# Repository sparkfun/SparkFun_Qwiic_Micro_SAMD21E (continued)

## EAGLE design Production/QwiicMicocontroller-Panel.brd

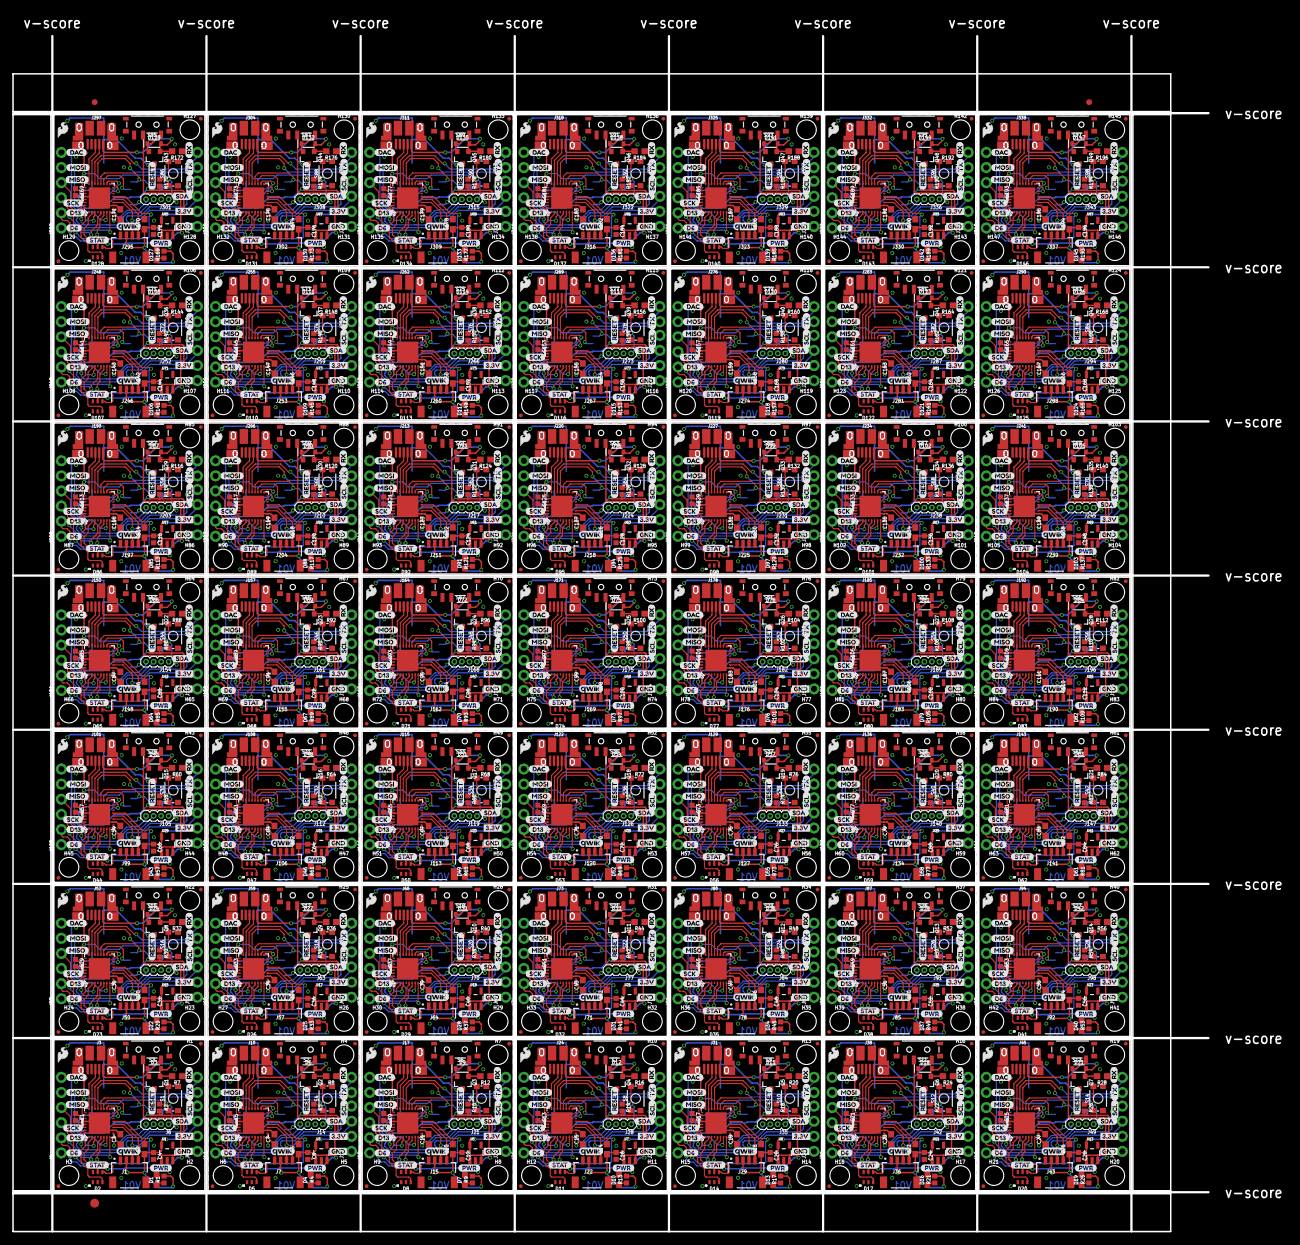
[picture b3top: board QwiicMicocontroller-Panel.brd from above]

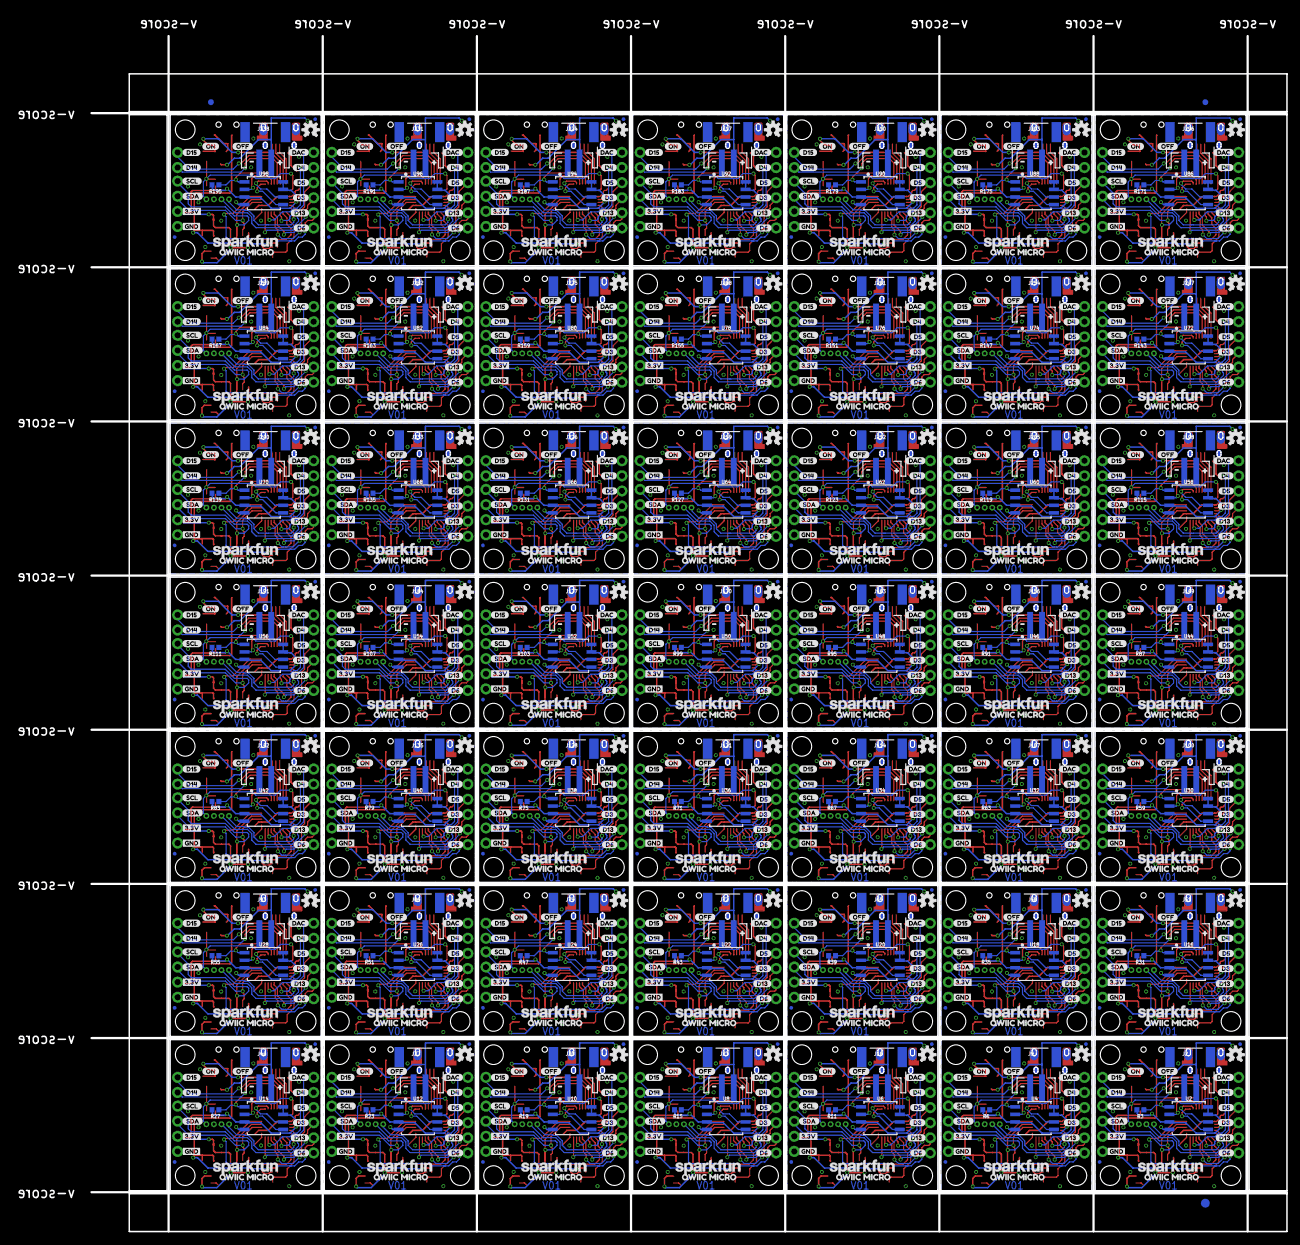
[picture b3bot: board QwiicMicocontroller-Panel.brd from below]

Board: 2 copper layers, 200.9 x 200.9 mm, 3387 parts (1179 on the bottom side), 1470 nets.

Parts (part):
C1, C4, C5, C8, C9, C12, C13, C16, C17, C20, C21, C24, C25, C28, C29, C32, C33, C36, C37, C40, C41, C44, C45, C48, C49, C52, C53, C56, C57, C60, C61, C64, C65, C68, C69, C72, C73, C76, C77, C80, C81, C84, C85, C88, C89, C92, C93, C96, C97, C100, C101, C104, C105, C108, C109, C112, C113, C116, C117, C120, C121, C124, C125, C128, C129, C132, C133, C136, C137, C140, C141, C144, C145, C148, C149, C152, C153, C156, C157, C160, C161, C164, C165, C168, C169, C172, C173, C176, C177, C180, C181, C184, C185, C188, C189, C192, C193, C196: 1.0uF; 0402
C2, C3, C6, C7, C10, C11, C14, C15, C18, C19, C22, C23, C26, C27, C30, C31, C34, C35, C38, C39, C42, C43, C46, C47, C50, C51, C54, C55, C58, C59, C62, C63, C66, C67, C70, C71, C74, C75, C78, C79, C82, C83, C86, C87, C90, C91, C94, C95, C98, C99, C102, C103, C106, C107, C110, C111, C114, C115, C118, C119, C122, C123, C126, C127, C130, C131, C134, C135, C138, C139, C142, C143, C146, C147, C150, C151, C154, C155, C158, C159, C162, C163, C166, C167, C170, C171, C174, C175, C178, C179, C182, C183, C186, C187, C190, C191, C194, C195: 10uF; 0603
D1, D4, D7, D10, D13, D16, D19, D22, D25, D28, D31, D34, D37, D40, D43, D46, D49, D52, D55, D58, D61, D64, D67, D70, D73, D76, D79, D82, D85, D88, D91, D94, D97, D100, D103, D106, D109, D112, D115, D118, D121, D124, D127, D130, D133, D136, D139, D142, D145: RED; LED-0603
D2, D5, D8, D11, D14, D17, D20, D23, D26, D29, D32, D35, D38, D41, D44, D47, D50, D53, D56, D59, D62, D65, D68, D71, D74, D77, D80, D83, D86, D89, D92, D95, D98, D101, D104, D107, D110, D113, D116, D119, D122, D125, D128, D131, D134, D137, D140, D143, D146: APA102-2020
D3, D6, D9, D12, D15, D18, D21, D24, D27, D30, D33, D36, D39, D42, D45, D48, D51, D54, D57, D60, D63, D66, D69, D72, D75, D78, D81, D84, D87, D90, D93, D96, D99, D102, D105, D108, D111, D114, D117, D120, D123, D126, D129, D132, D135, D138, D141, D144, D147: 1A/23V/620mV; SOD-323
E$1, E$2, E$3, E$4: FIDUCIAL-1X2
E$5, E$6: FIDUCIAL-1.5X3
FD1, FD2, FD3, FD4, FD5, FD6, FD7, FD8, FD9, FD10, FD11, FD12, FD13, FD14, FD15, FD16, FD17, FD18, FD19, FD20, FD21, FD22, FD23, FD24, FD25, FD26, FD27, FD28, FD29, FD30, FD31, FD32, FD33, FD34, FD35, FD36, FD37, FD38, FD39, FD40, FD41, FD42, FD43, FD44, FD45, FD46, FD47, FD48, FD49, FD50, FD51, FD52, FD53, FD54, FD55, FD56, FD57, FD58, FD59, FD60, FD61, FD62, FD63, FD64, FD65, FD66, FD67, FD68, FD69, FD70, FD71, FD72, FD73, FD74, FD75, FD76, FD77, FD78, FD79, FD80, FD81, FD82, FD83, FD84, FD85, FD86, FD87, FD88, FD89, FD90, FD91, FD92, FD93, FD94, FD95, FD96, FD97, FD98, FD99, FD100, FD101, FD102, FD103, FD104, FD105, FD106, FD107, FD108, FD109, FD110, FD111, FD112, FD113, FD114, FD115, FD116, FD117, FD118, FD119, FD120, FD121, FD122, FD123, FD124, FD125, FD126, FD127, FD128, FD129, FD130, FD131, FD132, FD133, FD134, FD135, FD136, FD137, FD138, FD139, FD140, FD141, FD142, FD143, FD144, FD145, FD146, FD147, FD148, FD149, FD150, FD151, FD152, FD153, FD154, FD155, FD156, FD157, FD158, FD159, FD160, FD161, FD162, FD163, FD164, FD165, FD166, FD167, FD168, FD169, FD170, FD171, FD172, FD173, FD174, FD175, FD176, FD177, FD178, FD179, FD180, FD181, FD182, FD183, FD184, FD185, FD186, FD187, FD188, FD189, FD190, FD191, FD192, FD193, FD194, FD195, FD196: FIDUCIALUFIDUCIAL; FIDUCIAL-MICRO
H1, H2, H3, H4, H5, H6, H7, H8, H9, H10, H11, H12, H13, H14, H15, H16, H17, H18, H19, H20, H21, H22, H23, H24, H25, H26, H27, H28, H29, H30, H31, H32, H33, H34, H35, H36, H37, H38, H39, H40, H41, H42, H43, H44, H45, H46, H47, H48, H49, H50, H51, H52, H53, H54, H55, H56, H57, H58, H59, H60, H61, H62, H63, H64, H65, H66, H67, H68, H69, H70, H71, H72, H73, H74, H75, H76, H77, H78, H79, H80, H81, H82, H83, H84, H85, H86, H87, H88, H89, H90, H91, H92, H93, H94, H95, H96, H97, H98, H99, H100, H101, H102, H103, H104, H105, H106, H107, H108, H109, H110, H111, H112, H113, H114, H115, H116, H117, H118, H119, H120, H121, H122, H123, H124, H125, H126, H127, H128, H129, H130, H131, H132, H133, H134, H135, H136, H137, H138, H139, H140, H141, H142, H143, H144, H145, H146, H147: STAND-OFF
J1, J7, J15, J22, J29, J36, J43, J50, J57, J64, J71, J78, J85, J92, J99, J106, J113, J120, J127, J134, J141, J148, J155, J162, J169, J176, J183, J190, J197, J204, J211, J218, J225, J232, J239, J246, J253, J260, J267, J274, J281, J288, J295, J302, J309, J316, J323, J330, J337: JST04_1MM_RA
J2, J9, J16, J23, J30, J37, J44, J51, J58, J65, J72, J79, J86, J93, J100, J107, J114, J121, J128, J135, J142, J149, J156, J163, J170, J177, J184, J191, J198, J205, J212, J219, J226, J233, J240, J247, J254, J261, J268, J275, J282, J289, J296, J303, J310, J317, J324, J331, J338: JST-2-SMD
J3, J10, J17, J24, J31, J38, J45, J52, J59, J66, J73, J80, J87, J94, J101, J108, J115, J122, J129, J136, J143, J150, J157, J164, J171, J178, J185, J192, J199, J206, J213, J220, J227, J234, J241, J248, J255, J262, J269, J276, J283, J290, J297, J304, J311, J318, J325, J332, J339: USB-MICROB-PTH-MILL
J4, J11, J18, J25, J32, J39, J46, J53, J60, J67, J74, J81, J88, J95, J102, J109, J116, J123, J130, J137, J144, J151, J158, J165, J172, J179, J186, J193, J200, J207, J214, J221, J228, J235, J242, J249, J256, J263, J270, J277, J284, J291, J298, J305, J312, J319, J326, J333, J340: 1X06_NO_SILK
J5, J12, J19, J26, J33, J40, J47, J54, J61, J68, J75, J82, J89, J96, J103, J110, J117, J124, J131, J138, J145, J152, J159, J166, J173, J180, J187, J194, J201, J208, J215, J222, J229, J236, J243, J250, J257, J264, J271, J278, J285, J292, J299, J306, J313, J320, J327, J334, J341: 1X02_NO_SILK
J6, J14, J21, J28, J35, J42, J49, J56, J63, J70, J77, J84, J91, J98, J105, J112, J119, J126, J133, J140, J147, J154, J161, J168, J175, J182, J189, J196, J203, J210, J217, J224, J231, J238, J245, J252, J259, J266, J273, J280, J287, J294, J301, J308, J315, J322, J329, J336, J343: 1X04_1.27MM
J8, J13, J20, J27, J34, J41, J48, J55, J62, J69, J76, J83, J90, J97, J104, J111, J118, J125, J132, J139, J146, J153, J160, J167, J174, J181, J188, J195, J202, J209, J216, J223, J230, J237, J244, J251, J258, J265, J272, J279, J286, J293, J300, J307, J314, J321, J328, J335, J342: 1X04_NO_SILK
LOGO1, LOGO4, LOGO7, LOGO10, LOGO13, LOGO16, LOGO19, LOGO22, LOGO25, LOGO28, LOGO31, LOGO34, LOGO37, LOGO40, LOGO43, LOGO46, LOGO49, LOGO52, LOGO55, LOGO58, LOGO61, LOGO64, LOGO67, LOGO70, LOGO73, LOGO76, LOGO79, LOGO82, LOGO85, LOGO88, LOGO91, LOGO94, LOGO97, LOGO100, LOGO103, LOGO106, LOGO109, LOGO112, LOGO115, LOGO118, LOGO121, LOGO124, LOGO127, LOGO130, LOGO133, LOGO136, LOGO139, LOGO142, LOGO145: OSHW-LOGOS; OSHW-LOGO-S
LOGO2, LOGO6, LOGO9, LOGO12, LOGO15, LOGO18, LOGO21, LOGO24, LOGO27, LOGO30, LOGO33, LOGO36, LOGO39, LOGO42, LOGO45, LOGO48, LOGO51, LOGO54, LOGO57, LOGO60, LOGO63, LOGO66, LOGO69, LOGO72, LOGO75, LOGO78, LOGO81, LOGO84, LOGO87, LOGO90, LOGO93, LOGO96, LOGO99, LOGO102, LOGO105, LOGO108, LOGO111, LOGO114, LOGO117, LOGO120, LOGO123, LOGO126, LOGO129, LOGO132, LOGO135, LOGO138, LOGO141, LOGO144, LOGO147: SFE_LOGO_NAME.1_INCH; SFE_LOGO_NAME_.1
LOGO3, LOGO5, LOGO8, LOGO11, LOGO14, LOGO17, LOGO20, LOGO23, LOGO26, LOGO29, LOGO32, LOGO35, LOGO38, LOGO41, LOGO44, LOGO47, LOGO50, LOGO53, LOGO56, LOGO59, LOGO62, LOGO65, LOGO68, LOGO71, LOGO74, LOGO77, LOGO80, LOGO83, LOGO86, LOGO89, LOGO92, LOGO95, LOGO98, LOGO101, LOGO104, LOGO107, LOGO110, LOGO113, LOGO116, LOGO119, LOGO122, LOGO125, LOGO128, LOGO131, LOGO134, LOGO137, LOGO140, LOGO143, LOGO146: SFE_LOGO_FLAME.1_INCH; SFE_LOGO_FLAME_.1
Q1, Q2, Q3, Q4, Q5, Q6, Q7, Q8, Q9, Q10, Q11, Q12, Q13, Q14, Q15, Q16, Q17, Q18, Q19, Q20, Q21, Q22, Q23, Q24, Q25, Q26, Q27, Q28, Q29, Q30, Q31, Q32, Q33, Q34, Q35, Q36, Q37, Q38, Q39, Q40, Q41, Q42, Q43, Q44, Q45, Q46, Q47, Q48, Q49: 2.5A/30V/105mΩ; SOT23-3
R1, R4, R9, R13, R17, R21, R25, R29, R33, R37, R41, R45, R49, R53, R57, R61, R65, R69, R73, R77, R81, R85, R89, R93, R97, R101, R105, R109, R113, R117, R121, R125, R129, R133, R137, R141, R145, R149, R153, R157, R161, R165, R169, R173, R177, R181, R185, R189, R193: 1K; 0402
R2, R3, R5, R6, R10, R11, R14, R15, R18, R19, R22, R23, R26, R27, R30, R31, R34, R35, R38, R39, R42, R43, R46, R47, R50, R51, R54, R55, R58, R59, R62, R63, R66, R67, R70, R71, R74, R75, R78, R79, R82, R83, R86, R87, R90, R91, R94, R95, R98, R99, R102, R103, R106, R107, R110, R111, R114, R115, R118, R119, R122, R123, R126, R127, R130, R131, R134, R135, R138, R139, R142, R143, R146, R147, R150, R151, R154, R155, R158, R159, R162, R163, R166, R167, R170, R171, R174, R175, R178, R179, R182, R183, R186, R187, R190, R191, R194, R195: 10k; 0402
R7, R8, R12, R16, R20, R24, R28, R32, R36, R40, R44, R48, R52, R56, R60, R64, R68, R72, R76, R80, R84, R88, R92, R96, R100, R104, R108, R112, R116, R120, R124, R128, R132, R136, R140, R144, R148, R152, R156, R160, R164, R168, R172, R176, R180, R184, R188, R192, R196: 10k; 0603
S1, S4, S6, S8, S10, S12, S14, S16, S18, S20, S22, S24, S26, S28, S30, S32, S34, S36, S38, S40, S42, S44, S46, S48, S50, S52, S54, S56, S58, S60, S62, S64, S66, S68, S70, S72, S74, S76, S78, S80, S82, S84, S86, S88, S90, S92, S94, S96, S98: MOMENTARY-SWITCH-SPST-SMD-4.6X2.8MM; TACTILE_SWITCH_SMD_4.6X2.8MM
S2, S3, S5, S7, S9, S11, S13, S15, S17, S19, S21, S23, S25, S27, S29, S31, S33, S35, S37, S39, S41, S43, S45, S47, S49, S51, S53, S55, S57, S59, S61, S63, S65, S67, S69, S71, S73, S75, S77, S79, S81, S83, S85, S87, S89, S91, S93, S95, S97: SWITCH_SPST_SMD_A
SAMD21E1, SAMD21E2, SAMD21E3, SAMD21E4, SAMD21E5, SAMD21E6, SAMD21E7, SAMD21E8, SAMD21E9, SAMD21E10, SAMD21E11, SAMD21E12, SAMD21E13, SAMD21E14, SAMD21E15, SAMD21E16, SAMD21E17, SAMD21E18, SAMD21E19, SAMD21E20, SAMD21E21, SAMD21E22, SAMD21E23, SAMD21E24, SAMD21E25, SAMD21E26, SAMD21E27, SAMD21E28, SAMD21E29, SAMD21E30, SAMD21E31, SAMD21E32, SAMD21E33, SAMD21E34, SAMD21E35, SAMD21E36, SAMD21E37, SAMD21E38, SAMD21E39, SAMD21E40, SAMD21E41, SAMD21E42, SAMD21E43, SAMD21E44, SAMD21E45, SAMD21E46, SAMD21E47, SAMD21E48, SAMD21E49: SAMD32E; QFN32
TP1, TP2, TP3, TP4, TP5, TP6, TP7, TP8, TP9, TP10, TP11, TP12, TP13, TP14, TP15, TP16, TP17, TP18, TP19, TP20, TP21, TP22, TP23, TP24, TP25, TP26, TP27, TP28, TP29, TP30, TP31, TP32, TP33, TP34, TP35, TP36, TP37, TP38, TP39, TP40, TP41, TP42, TP43, TP44, TP45, TP46, TP47, TP48, TP49, TP50, TP51, TP52, TP53, TP54, TP55, TP56, TP57, TP58, TP59, TP60, TP61, TP62, TP63, TP64, TP65, TP66, TP67, TP68, TP69, TP70, TP71, TP72, TP73, TP74, TP75, TP76, TP77, TP78, TP79, TP80, TP81, TP82, TP83, TP84, TP85, TP86, TP87, TP88, TP89, TP90, TP91, TP92, TP93, TP94, TP95, TP96, TP97, TP98: TEST-POINTTP_15TH_THRU; TP_15TH
U1, U3, U5, U7, U9, U11, U13, U15, U17, U19, U21, U23, U25, U27, U29, U31, U33, U35, U37, U39, U41, U43, U45, U47, U49, U51, U53, U55, U57, U59, U61, U63, U65, U67, U69, U71, U73, U75, U77, U79, U81, U83, U85, U87, U89, U91, U93, U95, U97: 3.3V; SOT23-5
U2, U4, U6, U8, U10, U12, U14, U16, U18, U20, U22, U24, U26, U28, U30, U32, U34, U36, U38, U40, U42, U44, U46, U48, U50, U52, U54, U56, U58, U60, U62, U64, U66, U68, U70, U72, U74, U76, U78, U80, U82, U84, U86, U88, U90, U92, U94, U96, U98: W25Q32FV; SOIC-8
U$1, U$64, U$97, U$130, U$163, U$196, U$229, U$262, U$295, U$328, U$361, U$394, U$427, U$460, U$493, U$526, U$559, U$592, U$625, U$658, U$691, U$724, U$757, U$790, U$823, U$856, U$889, U$922, U$955, U$988, U$1021, U$1054, U$1087, U$1120, U$1153, U$1186, U$1219, U$1252, U$1285, U$1318, U$1351, U$1384, U$1417, U$1450, U$1483, U$1516, U$1549, U$1582, U$1615: QWIIC_LOGO_4MM; QWIIC_4MM
U$2, U$5, U$23, U$50, U$67, U$83, U$100, U$116, U$133, U$149, U$166, U$182, U$199, U$215, U$232, U$248, U$265, U$281, U$298, U$314, U$331, U$347, U$364, U$380, U$397, U$413, U$430, U$446, U$463, U$479, U$496, U$512, U$529, U$545, U$562, U$578, U$595, U$611, U$628, U$644, U$661, U$677, U$694, U$710, U$727, U$743, U$760, U$776, U$793, U$809, U$826, U$842, U$859, U$875, U$892, U$908, U$925, U$941, U$958, U$974, U$991, U$1007, U$1024, U$1040, U$1057, U$1073, U$1090, U$1106, U$1123, U$1139, U$1156, U$1172, U$1189, U$1205, U$1222, U$1238, U$1255, U$1271, U$1288, U$1304, U$1321, U$1337, U$1354, U$1370, U$1387, U$1403, U$1420, U$1436, U$1453, U$1469, U$1486, U$1502, U$1519, U$1535, U$1552, U$1568, U$1585, U$1601: 3#3V1
U$3, U$65, U$98, U$131, U$164, U$197, U$230, U$263, U$296, U$329, U$362, U$395, U$428, U$461, U$494, U$527, U$560, U$593, U$626, U$659, U$692, U$725, U$758, U$791, U$824, U$857, U$890, U$923, U$956, U$989, U$1022, U$1055, U$1088, U$1121, U$1154, U$1187, U$1220, U$1253, U$1286, U$1319, U$1352, U$1385, U$1418, U$1451, U$1484, U$1517, U$1550, U$1583, U$1616: #23
U$4, U$66, U$99, U$132, U$165, U$198, U$231, U$264, U$297, U$330, U$363, U$396, U$429, U$462, U$495, U$528, U$561, U$594, U$627, U$660, U$693, U$726, U$759, U$792, U$825, U$858, U$891, U$924, U$957, U$990, U$1023, U$1056, U$1089, U$1122, U$1155, U$1188, U$1221, U$1254, U$1287, U$1320, U$1353, U$1386, U$1419, U$1452, U$1485, U$1518, U$1551, U$1584, U$1617: #24
U$6, U$10, U$29, U$56, U$68, U$89, U$101, U$122, U$134, U$155, U$167, U$188, U$200, U$221, U$233, U$254, U$266, U$287, U$299, U$320, U$332, U$353, U$365, U$386, U$398, U$419, U$431, U$452, U$464, U$485, U$497, U$518, U$530, U$551, U$563, U$584, U$596, U$617, U$629, U$650, U$662, U$683, U$695, U$716, U$728, U$749, U$761, U$782, U$794, U$815, U$827, U$848, U$860, U$881, U$893, U$914, U$926, U$947, U$959, U$980, U$992, U$1013, U$1025, U$1046, U$1058, U$1079, U$1091, U$1112, U$1124, U$1145, U$1157, U$1178, U$1190, U$1211, U$1223, U$1244, U$1256, U$1277, U$1289, U$1310, U$1322, U$1343, U$1355, U$1376, U$1388, U$1409, U$1421, U$1442, U$1454, U$1475, U$1487, U$1508, U$1520, U$1541, U$1553, U$1574, U$1586, U$1607: D139
U$7, U$36, U$69, U$102, U$135, U$168, U$201, U$234, U$267, U$300, U$333, U$366, U$399, U$432, U$465, U$498, U$531, U$564, U$597, U$630, U$663, U$696, U$729, U$762, U$795, U$828, U$861, U$894, U$927, U$960, U$993, U$1026, U$1059, U$1092, U$1125, U$1158, U$1191, U$1224, U$1257, U$1290, U$1323, U$1356, U$1389, U$1422, U$1455, U$1488, U$1521, U$1554, U$1587: D144
U$8, U$37, U$70, U$103, U$136, U$169, U$202, U$235, U$268, U$301, U$334, U$367, U$400, U$433, U$466, U$499, U$532, U$565, U$598, U$631, U$664, U$697, U$730, U$763, U$796, U$829, U$862, U$895, U$928, U$961, U$994, U$1027, U$1060, U$1093, U$1126, U$1159, U$1192, U$1225, U$1258, U$1291, U$1324, U$1357, U$1390, U$1423, U$1456, U$1489, U$1522, U$1555, U$1588: D155
U$9, U$30, U$38, U$57, U$71, U$90, U$104, U$123, U$137, U$156, U$170, U$189, U$203, U$222, U$236, U$255, U$269, U$288, U$302, U$321, U$335, U$354, U$368, U$387, U$401, U$420, U$434, U$453, U$467, U$486, U$500, U$519, U$533, U$552, U$566, U$585, U$599, U$618, U$632, U$651, U$665, U$684, U$698, U$717, U$731, U$750, U$764, U$783, U$797, U$816, U$830, U$849, U$863, U$882, U$896, U$915, U$929, U$948, U$962, U$981, U$995, U$1014, U$1028, U$1047, U$1061, U$1080, U$1094, U$1113, U$1127, U$1146, U$1160, U$1179, U$1193, U$1212, U$1226, U$1245, U$1259, U$1278, U$1292, U$1311, U$1325, U$1344, U$1358, U$1377, U$1391, U$1410, U$1424, U$1443, U$1457, U$1476, U$1490, U$1509, U$1523, U$1542, U$1556, U$1575, U$1589, U$1608: D610
U$11, U$25, U$39, U$52, U$72, U$85, U$105, U$118, U$138, U$151, U$171, U$184, U$204, U$217, U$237, U$250, U$270, U$283, U$303, U$316, U$336, U$349, U$369, U$382, U$402, U$415, U$435, U$448, U$468, U$481, U$501, U$514, U$534, U$547, U$567, U$580, U$600, U$613, U$633, U$646, U$666, U$679, U$699, U$712, U$732, U$745, U$765, U$778, U$798, U$811, U$831, U$844, U$864, U$877, U$897, U$910, U$930, U$943, U$963, U$976, U$996, U$1009, U$1029, U$1042, U$1062, U$1075, U$1095, U$1108, U$1128, U$1141, U$1161, U$1174, U$1194, U$1207, U$1227, U$1240, U$1260, U$1273, U$1293, U$1306, U$1326, U$1339, U$1359, U$1372, U$1392, U$1405, U$1425, U$1438, U$1458, U$1471, U$1491, U$1504, U$1524, U$1537, U$1557, U$1570, U$1590, U$1603: DAC11
U$12, U$58, U$91, U$124, U$157, U$190, U$223, U$256, U$289, U$322, U$355, U$388, U$421, U$454, U$487, U$520, U$553, U$586, U$619, U$652, U$685, U$718, U$751, U$784, U$817, U$850, U$883, U$916, U$949, U$982, U$1015, U$1048, U$1081, U$1114, U$1147, U$1180, U$1213, U$1246, U$1279, U$1312, U$1345, U$1378, U$1411, U$1444, U$1477, U$1510, U$1543, U$1576, U$1609: RESET22
U$13, U$24, U$40, U$51, U$73, U$84, U$106, U$117, U$139, U$150, U$172, U$183, U$205, U$216, U$238, U$249, U$271, U$282, U$304, U$315, U$337, U$348, U$370, U$381, U$403, U$414, U$436, U$447, U$469, U$480, U$502, U$513, U$535, U$546, U$568, U$579, U$601, U$612, U$634, U$645, U$667, U$678, U$700, U$711, U$733, U$744, U$766, U$777, U$799, U$810, U$832, U$843, U$865, U$876, U$898, U$909, U$931, U$942, U$964, U$975, U$997, U$1008, U$1030, U$1041, U$1063, U$1074, U$1096, U$1107, U$1129, U$1140, U$1162, U$1173, U$1195, U$1206, U$1228, U$1239, U$1261, U$1272, U$1294, U$1305, U$1327, U$1338, U$1360, U$1371, U$1393, U$1404, U$1426, U$1437, U$1459, U$1470, U$1492, U$1503, U$1525, U$1536, U$1558, U$1569, U$1591, U$1602: GND0
U$14, U$41, U$74, U$107, U$140, U$173, U$206, U$239, U$272, U$305, U$338, U$371, U$404, U$437, U$470, U$503, U$536, U$569, U$602, U$635, U$668, U$701, U$734, U$767, U$800, U$833, U$866, U$899, U$932, U$965, U$998, U$1031, U$1064, U$1097, U$1130, U$1163, U$1196, U$1229, U$1262, U$1295, U$1328, U$1361, U$1394, U$1427, U$1460, U$1493, U$1526, U$1559, U$1592: PWR14
U$15, U$42, U$75, U$108, U$141, U$174, U$207, U$240, U$273, U$306, U$339, U$372, U$405, U$438, U$471, U$504, U$537, U$570, U$603, U$636, U$669, U$702, U$735, U$768, U$801, U$834, U$867, U$900, U$933, U$966, U$999, U$1032, U$1065, U$1098, U$1131, U$1164, U$1197, U$1230, U$1263, U$1296, U$1329, U$1362, U$1395, U$1428, U$1461, U$1494, U$1527, U$1560, U$1593: QWIIC_MICRO16
U$16, U$43, U$76, U$109, U$142, U$175, U$208, U$241, U$274, U$307, U$340, U$373, U$406, U$439, U$472, U$505, U$538, U$571, U$604, U$637, U$670, U$703, U$736, U$769, U$802, U$835, U$868, U$901, U$934, U$967, U$1000, U$1033, U$1066, U$1099, U$1132, U$1165, U$1198, U$1231, U$1264, U$1297, U$1330, U$1363, U$1396, U$1429, U$1462, U$1495, U$1528, U$1561, U$1594: RX12
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
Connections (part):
3.3V: C2.1, C4.1, J1.2, J8.2, R1.2, R2.2, R3.2, SAMD21E18.VDDIN, U1.5, U2.3, U2.7, U2.8
3.3V1: C6.1, C8.1, J7.2, J13.2, R4.2, R5.2, R6.2, SAMD21E1.VDDIN, U3.5, U4.3, U4.7, U4.8
3.3V2: C10.1, C12.1, J15.2, J20.2, R9.2, R10.2, R11.2, SAMD21E2.VDDIN, U5.5, U6.3, U6.7, U6.8
3.3V3: C14.1, C16.1, J22.2, J27.2, R13.2, R14.2, R15.2, SAMD21E3.VDDIN, U7.5, U8.3, U8.7, U8.8
3.3V4: C18.1, C20.1, J29.2, J34.2, R17.2, R18.2, R19.2, SAMD21E4.VDDIN, U9.5, U10.3, U10.7, U10.8
3.3V5: C22.1, C24.1, J36.2, J41.2, R21.2, R22.2, R23.2, SAMD21E5.VDDIN, U11.5, U12.3, U12.7, U12.8
3.3V6: C26.1, C28.1, J43.2, J48.2, R25.2, R26.2, R27.2, SAMD21E6.VDDIN, U13.5, U14.3, U14.7, U14.8
3.3V7: C30.1, C32.1, J50.2, J55.2, R29.2, R30.2, R31.2, SAMD21E7.VDDIN, U15.5, U16.3, U16.7, U16.8
3.3V8: C34.1, C36.1, J57.2, J62.2, R33.2, R34.2, R35.2, SAMD21E8.VDDIN, U17.5, U18.3, U18.7, U18.8
3.3V9: C38.1, C40.1, J64.2, J69.2, R37.2, R38.2, R39.2, SAMD21E9.VDDIN, U19.5, U20.3, U20.7, U20.8
3.3V10: C42.1, C44.1, J71.2, J76.2, R41.2, R42.2, R43.2, SAMD21E10.VDDIN, U21.5, U22.3, U22.7, U22.8
3.3V11: C46.1, C48.1, J78.2, J83.2, R45.2, R46.2, R47.2, SAMD21E11.VDDIN, U23.5, U24.3, U24.7, U24.8
3.3V12: C50.1, C52.1, J85.2, J90.2, R49.2, R50.2, R51.2, SAMD21E12.VDDIN, U25.5, U26.3, U26.7, U26.8
3.3V13: C54.1, C56.1, J92.2, J97.2, R53.2, R54.2, R55.2, SAMD21E13.VDDIN, U27.5, U28.3, U28.7, U28.8
3.3V14: C58.1, C60.1, J99.2, J104.2, R57.2, R58.2, R59.2, SAMD21E14.VDDIN, U29.5, U30.3, U30.7, U30.8
3.3V15: C62.1, C64.1, J106.2, J111.2, R61.2, R62.2, R63.2, SAMD21E15.VDDIN, U31.5, U32.3, U32.7, U32.8
3.3V16: C66.1, C68.1, J113.2, J118.2, R65.2, R66.2, R67.2, SAMD21E16.VDDIN, U33.5, U34.3, U34.7, U34.8
3.3V17: C70.1, C72.1, J120.2, J125.2, R69.2, R70.2, R71.2, SAMD21E17.VDDIN, U35.5, U36.3, U36.7, U36.8
3.3V18: C74.1, C76.1, J127.2, J132.2, R73.2, R74.2, R75.2, SAMD21E19.VDDIN, U37.5, U38.3, U38.7, U38.8
3.3V19: C78.1, C80.1, J134.2, J139.2, R77.2, R78.2, R79.2, SAMD21E20.VDDIN, U39.5, U40.3, U40.7, U40.8
3.3V20: C82.1, C84.1, J141.2, J146.2, R81.2, R82.2, R83.2, SAMD21E21.VDDIN, U41.5, U42.3, U42.7, U42.8
3.3V21: C86.1, C88.1, J148.2, J153.2, R85.2, R86.2, R87.2, SAMD21E22.VDDIN, U43.5, U44.3, U44.7, U44.8
3.3V22: C90.1, C92.1, J155.2, J160.2, R89.2, R90.2, R91.2, SAMD21E23.VDDIN, U45.5, U46.3, U46.7, U46.8
3.3V23: C94.1, C96.1, J162.2, J167.2, R93.2, R94.2, R95.2, SAMD21E24.VDDIN, U47.5, U48.3, U48.7, U48.8
3.3V24: C98.1, C100.1, J169.2, J174.2, R97.2, R98.2, R99.2, SAMD21E25.VDDIN, U49.5, U50.3, U50.7, U50.8
3.3V25: C102.1, C104.1, J176.2, J181.2, R101.2, R102.2, R103.2, SAMD21E26.VDDIN, U51.5, U52.3, U52.7, U52.8
3.3V26: C106.1, C108.1, J183.2, J188.2, R105.2, R106.2, R107.2, SAMD21E27.VDDIN, U53.5, U54.3, U54.7, U54.8
3.3V27: C110.1, C112.1, J190.2, J195.2, R109.2, R110.2, R111.2, SAMD21E28.VDDIN, U55.5, U56.3, U56.7, U56.8
3.3V28: C114.1, C116.1, J197.2, J202.2, R113.2, R114.2, R115.2, SAMD21E29.VDDIN, U57.5, U58.3, U58.7, U58.8
3.3V29: C118.1, C120.1, J204.2, J209.2, R117.2, R118.2, R119.2, SAMD21E30.VDDIN, U59.5, U60.3, U60.7, U60.8
3.3V30: C122.1, C124.1, J211.2, J216.2, R121.2, R122.2, R123.2, SAMD21E31.VDDIN, U61.5, U62.3, U62.7, U62.8
3.3V31: C126.1, C128.1, J218.2, J223.2, R125.2, R126.2, R127.2, SAMD21E32.VDDIN, U63.5, U64.3, U64.7, U64.8
3.3V32: C130.1, C132.1, J225.2, J230.2, R129.2, R130.2, R131.2, SAMD21E33.VDDIN, U65.5, U66.3, U66.7, U66.8
3.3V33: C134.1, C136.1, J232.2, J237.2, R133.2, R134.2, R135.2, SAMD21E34.VDDIN, U67.5, U68.3, U68.7, U68.8
3.3V34: C138.1, C140.1, J239.2, J244.2, R137.2, R138.2, R139.2, SAMD21E35.VDDIN, U69.5, U70.3, U70.7, U70.8
3.3V35: C142.1, C144.1, J246.2, J251.2, R141.2, R142.2, R143.2, SAMD21E36.VDDIN, U71.5, U72.3, U72.7, U72.8
3.3V36: C146.1, C148.1, J253.2, J258.2, R145.2, R146.2, R147.2, SAMD21E37.VDDIN, U73.5, U74.3, U74.7, U74.8
3.3V37: C150.1, C152.1, J260.2, J265.2, R149.2, R150.2, R151.2, SAMD21E38.VDDIN, U75.5, U76.3, U76.7, U76.8
3.3V38: C154.1, C156.1, J267.2, J272.2, R153.2, R154.2, R155.2, SAMD21E39.VDDIN, U77.5, U78.3, U78.7, U78.8
3.3V39: C158.1, C160.1, J274.2, J279.2, R157.2, R158.2, R159.2, SAMD21E40.VDDIN, U79.5, U80.3, U80.7, U80.8
3.3V40: C162.1, C164.1, J281.2, J286.2, R161.2, R162.2, R163.2, SAMD21E41.VDDIN, U81.5, U82.3, U82.7, U82.8
3.3V41: C166.1, C168.1, J288.2, J293.2, R165.2, R166.2, R167.2, SAMD21E42.VDDIN, U83.5, U84.3, U84.7, U84.8
3.3V42: C170.1, C172.1, J295.2, J300.2, R169.2, R170.2, R171.2, SAMD21E43.VDDIN, U85.5, U86.3, U86.7, U86.8
3.3V43: C174.1, C176.1, J302.2, J307.2, R173.2, R174.2, R175.2, SAMD21E44.VDDIN, U87.5, U88.3, U88.7, U88.8
3.3V44: C178.1, C180.1, J309.2, J314.2, R177.2, R178.2, R179.2, SAMD21E45.VDDIN, U89.5, U90.3, U90.7, U90.8
3.3V45: C182.1, C184.1, J316.2, J321.2, R181.2, R182.2, R183.2, SAMD21E46.VDDIN, U91.5, U92.3, U92.7, U92.8
3.3V46: C186.1, C188.1, J323.2, J328.2, R185.2, R186.2, R187.2, SAMD21E47.VDDIN, U93.5, U94.3, U94.7, U94.8
3.3V47: C190.1, C192.1, J330.2, J335.2, R189.2, R190.2, R191.2, SAMD21E48.VDDIN, U95.5, U96.3, U96.7, U96.8
3.3V48: C194.1, C196.1, J337.2, J342.2, R193.2, R194.2, R195.2, SAMD21E49.VDDIN, U97.5, U98.3, U98.7, U98.8
!RESET: J6.1, R2.1, S1.3, S1.4, SAMD21E18.NRESET
!RESET1: J14.1, R5.1, S4.3, S4.4, SAMD21E1.NRESET
!RESET2: J21.1, R10.1, S6.3, S6.4, SAMD21E2.NRESET
!RESET3: J28.1, R14.1, S8.3, S8.4, SAMD21E3.NRESET
!RESET4: J35.1, R18.1, S10.3, S10.4, SAMD21E4.NRESET
!RESET5: J42.1, R22.1, S12.3, S12.4, SAMD21E5.NRESET
!RESET6: J49.1, R26.1, S14.3, S14.4, SAMD21E6.NRESET
!RESET7: J56.1, R30.1, S16.3, S16.4, SAMD21E7.NRESET
!RESET8: J63.1, R34.1, S18.3, S18.4, SAMD21E8.NRESET
!RESET9: J70.1, R38.1, S20.3, S20.4, SAMD21E9.NRESET
!RESET10: J77.1, R42.1, S22.3, S22.4, SAMD21E10.NRESET
!RESET11: J84.1, R46.1, S24.3, S24.4, SAMD21E11.NRESET
!RESET12: J91.1, R50.1, S26.3, S26.4, SAMD21E12.NRESET
!RESET13: J98.1, R54.1, S28.3, S28.4, SAMD21E13.NRESET
!RESET14: J105.1, R58.1, S30.3, S30.4, SAMD21E14.NRESET
!RESET15: J112.1, R62.1, S32.3, S32.4, SAMD21E15.NRESET
!RESET16: J119.1, R66.1, S34.3, S34.4, SAMD21E16.NRESET
!RESET17: J126.1, R70.1, S36.3, S36.4, SAMD21E17.NRESET
!RESET18: J133.1, R74.1, S38.3, S38.4, SAMD21E19.NRESET
!RESET19: J140.1, R78.1, S40.3, S40.4, SAMD21E20.NRESET
!RESET20: J147.1, R82.1, S42.3, S42.4, SAMD21E21.NRESET
!RESET21: J154.1, R86.1, S44.3, S44.4, SAMD21E22.NRESET
!RESET22: J161.1, R90.1, S46.3, S46.4, SAMD21E23.NRESET
!RESET23: J168.1, R94.1, S48.3, S48.4, SAMD21E24.NRESET
!RESET24: J175.1, R98.1, S50.3, S50.4, SAMD21E25.NRESET
!RESET25: J182.1, R102.1, S52.3, S52.4, SAMD21E26.NRESET
!RESET26: J189.1, R106.1, S54.3, S54.4, SAMD21E27.NRESET
!RESET27: J196.1, R110.1, S56.3, S56.4, SAMD21E28.NRESET
!RESET28: J203.1, R114.1, S58.3, S58.4, SAMD21E29.NRESET
!RESET29: J210.1, R118.1, S60.3, S60.4, SAMD21E30.NRESET
!RESET30: J217.1, R122.1, S62.3, S62.4, SAMD21E31.NRESET
!RESET31: J224.1, R126.1, S64.3, S64.4, SAMD21E32.NRESET
!RESET32: J231.1, R130.1, S66.3, S66.4, SAMD21E33.NRESET
!RESET33: J238.1, R134.1, S68.3, S68.4, SAMD21E34.NRESET
!RESET34: J245.1, R138.1, S70.3, S70.4, SAMD21E35.NRESET
!RESET35: J252.1, R142.1, S72.3, S72.4, SAMD21E36.NRESET
!RESET36: J259.1, R146.1, S74.3, S74.4, SAMD21E37.NRESET
!RESET37: J266.1, R150.1, S76.3, S76.4, SAMD21E38.NRESET
!RESET38: J273.1, R154.1, S78.3, S78.4, SAMD21E39.NRESET
!RESET39: J280.1, R158.1, S80.3, S80.4, SAMD21E40.NRESET
!RESET40: J287.1, R162.1, S82.3, S82.4, SAMD21E41.NRESET
!RESET41: J294.1, R166.1, S84.3, S84.4, SAMD21E42.NRESET
!RESET42: J301.1, R170.1, S86.3, S86.4, SAMD21E43.NRESET
!RESET43: J308.1, R174.1, S88.3, S88.4, SAMD21E44.NRESET
!RESET44: J315.1, R178.1, S90.3, S90.4, SAMD21E45.NRESET
!RESET45: J322.1, R182.1, S92.3, S92.4, SAMD21E46.NRESET
!RESET46: J329.1, R186.1, S94.3, S94.4, SAMD21E47.NRESET
!RESET47: J336.1, R190.1, S96.3, S96.4, SAMD21E48.NRESET
!RESET48: J343.1, R194.1, S98.3, S98.4, SAMD21E49.NRESET
CI: D2.CKI, SAMD21E18.PA01
CI1: D5.CKI, SAMD21E1.PA01
CI2: D8.CKI, SAMD21E2.PA01
CI3: D11.CKI, SAMD21E3.PA01
CI4: D14.CKI, SAMD21E4.PA01
CI5: D17.CKI, SAMD21E5.PA01
CI6: D20.CKI, SAMD21E6.PA01
CI7: D23.CKI, SAMD21E7.PA01
CI8: D26.CKI, SAMD21E8.PA01
CI9: D29.CKI, SAMD21E9.PA01
CI10: D32.CKI, SAMD21E10.PA01
CI11: D35.CKI, SAMD21E11.PA01
CI12: D38.CKI, SAMD21E12.PA01
CI13: D41.CKI, SAMD21E13.PA01
CI14: D44.CKI, SAMD21E14.PA01
CI15: D47.CKI, SAMD21E15.PA01
CI16: D50.CKI, SAMD21E16.PA01
CI17: D53.CKI, SAMD21E17.PA01
CI18: D56.CKI, SAMD21E19.PA01
CI19: D59.CKI, SAMD21E20.PA01
CI20: D62.CKI, SAMD21E21.PA01
CI21: D65.CKI, SAMD21E22.PA01
CI22: D68.CKI, SAMD21E23.PA01
CI23: D71.CKI, SAMD21E24.PA01
CI24: D74.CKI, SAMD21E25.PA01
CI25: D77.CKI, SAMD21E26.PA01
CI26: D80.CKI, SAMD21E27.PA01
CI27: D83.CKI, SAMD21E28.PA01
CI28: D86.CKI, SAMD21E29.PA01
CI29: D89.CKI, SAMD21E30.PA01
CI30: D92.CKI, SAMD21E31.PA01
CI31: D95.CKI, SAMD21E32.PA01
CI32: D98.CKI, SAMD21E33.PA01
CI33: D101.CKI, SAMD21E34.PA01
CI34: D104.CKI, SAMD21E35.PA01
CI35: D107.CKI, SAMD21E36.PA01
CI36: D110.CKI, SAMD21E37.PA01
CI37: D113.CKI, SAMD21E38.PA01
CI38: D116.CKI, SAMD21E39.PA01
CI39: D119.CKI, SAMD21E40.PA01
CI40: D122.CKI, SAMD21E41.PA01
CI41: D125.CKI, SAMD21E42.PA01
CI42: D128.CKI, SAMD21E43.PA01
CI43: D131.CKI, SAMD21E44.PA01
CI44: D134.CKI, SAMD21E45.PA01
CI45: D137.CKI, SAMD21E46.PA01
CI46: D140.CKI, SAMD21E47.PA01
CI47: D143.CKI, SAMD21E48.PA01
CI48: D146.CKI, SAMD21E49.PA01
D1: J11.1, SAMD21E1.PA04
D2: J11.2, SAMD21E1.PA10
D3: J18.1, SAMD21E2.PA04
D4: J18.2, SAMD21E2.PA10
D5: J25.1, SAMD21E3.PA04
D6: J4.1, SAMD21E18.PA04
D7: J25.2, SAMD21E3.PA10
D8: J32.1, SAMD21E4.PA04
D9: J32.2, SAMD21E4.PA10
D10: J39.1, SAMD21E5.PA04
D11: J39.2, SAMD21E5.PA10
D12: J46.1, SAMD21E6.PA04
D13: J4.2, SAMD21E18.PA10
D14: J46.2, SAMD21E6.PA10
D15: J53.1, SAMD21E7.PA04
D16: J53.2, SAMD21E7.PA10
D17: J60.1, SAMD21E8.PA04
D18: J60.2, SAMD21E8.PA10
D19: J67.1, SAMD21E9.PA04
D20: J67.2, SAMD21E9.PA10
D21: J74.1, SAMD21E10.PA04
D22: J74.2, SAMD21E10.PA10
D23: J81.1, SAMD21E11.PA04
D24: J81.2, SAMD21E11.PA10
D25: J88.1, SAMD21E12.PA04
D26: J88.2, SAMD21E12.PA10
D27: J95.1, SAMD21E13.PA04
D28: J95.2, SAMD21E13.PA10
D29: J102.1, SAMD21E14.PA04
D30: J102.2, SAMD21E14.PA10
D31: J109.1, SAMD21E15.PA04
D32: J109.2, SAMD21E15.PA10
D33: J116.1, SAMD21E16.PA04
D34: J116.2, SAMD21E16.PA10
D35: J123.1, SAMD21E17.PA04
D36: J123.2, SAMD21E17.PA10
D37: J130.1, SAMD21E19.PA04
D38: J130.2, SAMD21E19.PA10
D39: J137.1, SAMD21E20.PA04
D40: J137.2, SAMD21E20.PA10
D41: J144.1, SAMD21E21.PA04
D42: J144.2, SAMD21E21.PA10
D43: J151.1, SAMD21E22.PA04
D44: J151.2, SAMD21E22.PA10
D45: J158.1, SAMD21E23.PA04
D46: J158.2, SAMD21E23.PA10
D47: J165.1, SAMD21E24.PA04
D48: J165.2, SAMD21E24.PA10
D49: J172.1, SAMD21E25.PA04
D50: J172.2, SAMD21E25.PA10
D51: J179.1, SAMD21E26.PA04
D52: J179.2, SAMD21E26.PA10
D53: J186.1, SAMD21E27.PA04
D54: J186.2, SAMD21E27.PA10
D55: J193.1, SAMD21E28.PA04
D56: J193.2, SAMD21E28.PA10
D57: J200.1, SAMD21E29.PA04
D58: J200.2, SAMD21E29.PA10
D59: J207.1, SAMD21E30.PA04
D60: J207.2, SAMD21E30.PA10
D61: J214.1, SAMD21E31.PA04
D62: J214.2, SAMD21E31.PA10
D63: J221.1, SAMD21E32.PA04
D64: J221.2, SAMD21E32.PA10
D65: J228.1, SAMD21E33.PA04
D66: J228.2, SAMD21E33.PA10
D67: J235.1, SAMD21E34.PA04
D68: J235.2, SAMD21E34.PA10
D69: J242.1, SAMD21E35.PA04
D70: J242.2, SAMD21E35.PA10
D71: J249.1, SAMD21E36.PA04
D72: J249.2, SAMD21E36.PA10
D73: J256.1, SAMD21E37.PA04
D74: J256.2, SAMD21E37.PA10
D75: J263.1, SAMD21E38.PA04
D76: J263.2, SAMD21E38.PA10
D77: J270.1, SAMD21E39.PA04
D78: J270.2, SAMD21E39.PA10
D79: J277.1, SAMD21E40.PA04
D80: J277.2, SAMD21E40.PA10
D81: J284.1, SAMD21E41.PA04
D82: J284.2, SAMD21E41.PA10
D83: J291.1, SAMD21E42.PA04
D84: J291.2, SAMD21E42.PA10
D85: J298.1, SAMD21E43.PA04
D86: J298.2, SAMD21E43.PA10
D87: J305.1, SAMD21E44.PA04
D88: J305.2, SAMD21E44.PA10
D89: J312.1, SAMD21E45.PA04
D90: J312.2, SAMD21E45.PA10
D91: J319.1, SAMD21E46.PA04
D92: J319.2, SAMD21E46.PA10
D93: J326.1, SAMD21E47.PA04
D94: J326.2, SAMD21E47.PA10
D95: J333.1, SAMD21E48.PA04
D96: J333.2, SAMD21E48.PA10
D97: J340.1, SAMD21E49.PA04
D98: J340.2, SAMD21E49.PA10
D+: J3.D+, SAMD21E18.PA25
D+1: J10.D+, SAMD21E1.PA25
D+2: J17.D+, SAMD21E2.PA25
D+3: J24.D+, SAMD21E3.PA25
D+4: J31.D+, SAMD21E4.PA25
D+5: J38.D+, SAMD21E5.PA25
D+6: J45.D+, SAMD21E6.PA25
D+7: J52.D+, SAMD21E7.PA25
D+8: J59.D+, SAMD21E8.PA25
D+9: J66.D+, SAMD21E9.PA25
D+10: J73.D+, SAMD21E10.PA25
D+11: J80.D+, SAMD21E11.PA25
D+12: J87.D+, SAMD21E12.PA25
D+13: J94.D+, SAMD21E13.PA25
D+14: J101.D+, SAMD21E14.PA25
D+15: J108.D+, SAMD21E15.PA25
D+16: J115.D+, SAMD21E16.PA25
D+17: J122.D+, SAMD21E17.PA25
D+18: J129.D+, SAMD21E19.PA25
D+19: J136.D+, SAMD21E20.PA25
D+20: J143.D+, SAMD21E21.PA25
D+21: J150.D+, SAMD21E22.PA25
D+22: J157.D+, SAMD21E23.PA25
D+23: J164.D+, SAMD21E24.PA25
D+24: J171.D+, SAMD21E25.PA25
D+25: J178.D+, SAMD21E26.PA25
D+26: J185.D+, SAMD21E27.PA25
D+27: J192.D+, SAMD21E28.PA25
D+28: J199.D+, SAMD21E29.PA25
D+29: J206.D+, SAMD21E30.PA25
D+30: J213.D+, SAMD21E31.PA25
D+31: J220.D+, SAMD21E32.PA25
D+32: J227.D+, SAMD21E33.PA25
D+33: J234.D+, SAMD21E34.PA25
D+34: J241.D+, SAMD21E35.PA25
D+35: J248.D+, SAMD21E36.PA25
D+36: J255.D+, SAMD21E37.PA25
D+37: J262.D+, SAMD21E38.PA25
D+38: J269.D+, SAMD21E39.PA25
D+39: J276.D+, SAMD21E40.PA25
D+40: J283.D+, SAMD21E41.PA25
D+41: J290.D+, SAMD21E42.PA25
D+42: J297.D+, SAMD21E43.PA25
D+43: J304.D+, SAMD21E44.PA25
D+44: J311.D+, SAMD21E45.PA25
D+45: J318.D+, SAMD21E46.PA25
D+46: J325.D+, SAMD21E47.PA25
D+47: J332.D+, SAMD21E48.PA25
D+48: J339.D+, SAMD21E49.PA25
D-: J3.D-, SAMD21E18.PA24
D-1: J10.D-, SAMD21E1.PA24
D-2: J17.D-, SAMD21E2.PA24
D-3: J24.D-, SAMD21E3.PA24
D-4: J31.D-, SAMD21E4.PA24
D-5: J38.D-, SAMD21E5.PA24
D-6: J45.D-, SAMD21E6.PA24
D-7: J52.D-, SAMD21E7.PA24
D-8: J59.D-, SAMD21E8.PA24
D-9: J66.D-, SAMD21E9.PA24
D-10: J73.D-, SAMD21E10.PA24
D-11: J80.D-, SAMD21E11.PA24
D-12: J87.D-, SAMD21E12.PA24
D-13: J94.D-, SAMD21E13.PA24
D-14: J101.D-, SAMD21E14.PA24
D-15: J108.D-, SAMD21E15.PA24
D-16: J115.D-, SAMD21E16.PA24
D-17: J122.D-, SAMD21E17.PA24
D-18: J129.D-, SAMD21E19.PA24
D-19: J136.D-, SAMD21E20.PA24
D-20: J143.D-, SAMD21E21.PA24
D-21: J150.D-, SAMD21E22.PA24
D-22: J157.D-, SAMD21E23.PA24
D-23: J164.D-, SAMD21E24.PA24
D-24: J171.D-, SAMD21E25.PA24
D-25: J178.D-, SAMD21E26.PA24
D-26: J185.D-, SAMD21E27.PA24
D-27: J192.D-, SAMD21E28.PA24
D-28: J199.D-, SAMD21E29.PA24
D-29: J206.D-, SAMD21E30.PA24
D-30: J213.D-, SAMD21E31.PA24
D-31: J220.D-, SAMD21E32.PA24
D-32: J227.D-, SAMD21E33.PA24
D-33: J234.D-, SAMD21E34.PA24
D-34: J241.D-, SAMD21E35.PA24
D-35: J248.D-, SAMD21E36.PA24
D-36: J255.D-, SAMD21E37.PA24
D-37: J262.D-, SAMD21E38.PA24
D-38: J269.D-, SAMD21E39.PA24
D-39: J276.D-, SAMD21E40.PA24
D-40: J283.D-, SAMD21E41.PA24
D-41: J290.D-, SAMD21E42.PA24
D-42: J297.D-, SAMD21E43.PA24
D-43: J304.D-, SAMD21E44.PA24
D-44: J311.D-, SAMD21E45.PA24
D-45: J318.D-, SAMD21E46.PA24
D-46: J325.D-, SAMD21E47.PA24
D-47: J332.D-, SAMD21E48.PA24
D-48: J339.D-, SAMD21E49.PA24
DAC: J4.6, SAMD21E18.PA02
DAC1: J11.6, SAMD21E1.PA02
DAC2: J18.6, SAMD21E2.PA02
DAC3: J25.6, SAMD21E3.PA02
DAC4: J32.6, SAMD21E4.PA02
DAC5: J39.6, SAMD21E5.PA02
DAC6: J46.6, SAMD21E6.PA02
DAC7: J53.6, SAMD21E7.PA02
DAC8: J60.6, SAMD21E8.PA02
DAC9: J67.6, SAMD21E9.PA02
DAC10: J74.6, SAMD21E10.PA02
DAC11: J81.6, SAMD21E11.PA02
DAC12: J88.6, SAMD21E12.PA02
DAC13: J95.6, SAMD21E13.PA02
DAC14: J102.6, SAMD21E14.PA02
DAC15: J109.6, SAMD21E15.PA02
DAC16: J116.6, SAMD21E16.PA02
DAC17: J123.6, SAMD21E17.PA02
DAC18: J130.6, SAMD21E19.PA02
DAC19: J137.6, SAMD21E20.PA02
DAC20: J144.6, SAMD21E21.PA02
DAC21: J151.6, SAMD21E22.PA02
DAC22: J158.6, SAMD21E23.PA02
DAC23: J165.6, SAMD21E24.PA02
DAC24: J172.6, SAMD21E25.PA02
DAC25: J179.6, SAMD21E26.PA02
DAC26: J186.6, SAMD21E27.PA02
DAC27: J193.6, SAMD21E28.PA02
DAC28: J200.6, SAMD21E29.PA02
DAC29: J207.6, SAMD21E30.PA02
DAC30: J214.6, SAMD21E31.PA02
DAC31: J221.6, SAMD21E32.PA02
DAC32: J228.6, SAMD21E33.PA02
DAC33: J235.6, SAMD21E34.PA02
DAC34: J242.6, SAMD21E35.PA02
DAC35: J249.6, SAMD21E36.PA02
DAC36: J256.6, SAMD21E37.PA02
DAC37: J263.6, SAMD21E38.PA02
DAC38: J270.6, SAMD21E39.PA02
DAC39: J277.6, SAMD21E40.PA02
DAC40: J284.6, SAMD21E41.PA02
DAC41: J291.6, SAMD21E42.PA02
DAC42: J298.6, SAMD21E43.PA02
DAC43: J305.6, SAMD21E44.PA02
DAC44: J312.6, SAMD21E45.PA02
DAC45: J319.6, SAMD21E46.PA02
DAC46: J326.6, SAMD21E47.PA02
DAC47: J333.6, SAMD21E48.PA02
DAC48: J340.6, SAMD21E49.PA02
DI: D2.SDI, SAMD21E18.PA00
DI1: D5.SDI, SAMD21E1.PA00
DI2: D8.SDI, SAMD21E2.PA00
DI3: D11.SDI, SAMD21E3.PA00
DI4: D14.SDI, SAMD21E4.PA00
DI5: D17.SDI, SAMD21E5.PA00
DI6: D20.SDI, SAMD21E6.PA00
DI7: D23.SDI, SAMD21E7.PA00
DI8: D26.SDI, SAMD21E8.PA00
DI9: D29.SDI, SAMD21E9.PA00
DI10: D32.SDI, SAMD21E10.PA00
DI11: D35.SDI, SAMD21E11.PA00
DI12: D38.SDI, SAMD21E12.PA00
DI13: D41.SDI, SAMD21E13.PA00
DI14: D44.SDI, SAMD21E14.PA00
DI15: D47.SDI, SAMD21E15.PA00
DI16: D50.SDI, SAMD21E16.PA00
DI17: D53.SDI, SAMD21E17.PA00
DI18: D56.SDI, SAMD21E19.PA00
DI19: D59.SDI, SAMD21E20.PA00
DI20: D62.SDI, SAMD21E21.PA00
DI21: D65.SDI, SAMD21E22.PA00
DI22: D68.SDI, SAMD21E23.PA00
DI23: D71.SDI, SAMD21E24.PA00
DI24: D74.SDI, SAMD21E25.PA00
DI25: D77.SDI, SAMD21E26.PA00
DI26: D80.SDI, SAMD21E27.PA00
DI27: D83.SDI, SAMD21E28.PA00
DI28: D86.SDI, SAMD21E29.PA00
DI29: D89.SDI, SAMD21E30.PA00
DI30: D92.SDI, SAMD21E31.PA00
DI31: D95.SDI, SAMD21E32.PA00
DI32: D98.SDI, SAMD21E33.PA00
DI33: D101.SDI, SAMD21E34.PA00
DI34: D104.SDI, SAMD21E35.PA00
DI35: D107.SDI, SAMD21E36.PA00
DI36: D110.SDI, SAMD21E37.PA00
DI37: D113.SDI, SAMD21E38.PA00
DI38: D116.SDI, SAMD21E39.PA00
DI39: D119.SDI, SAMD21E40.PA00
DI40: D122.SDI, SAMD21E41.PA00
DI41: D125.SDI, SAMD21E42.PA00
DI42: D128.SDI, SAMD21E43.PA00
DI43: D131.SDI, SAMD21E44.PA00
DI44: D134.SDI, SAMD21E45.PA00
DI45: D137.SDI, SAMD21E46.PA00
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
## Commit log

2019-07-22 Initial Commit - Moves files from old repo
2019-07-22 Improves all silk, replaces 0603 resistor with 0402, updates trace work for better ground pour
2019-07-23 Moves some traces
2019-07-23 Updates micro-controller symbol with Arduino digital pin assignments
    * replaces lipo battery symbol with better one
    * Re-adds battery line test ponit
    * Removes info text about Arduino pin assignments
    * Improves notes on SERCOM ports
    * Re-numbers all parts
    * Removes test library - no longer needed.
2019-07-23 Updates microcontroller symbol
2019-07-23 Moves some text around
2019-07-23 Attaches analog voltage pin to 3.3V power rail
2019-07-24 Moves silk around in various spots, rotates LED to make space for PWR silk
2019-07-25 Updates numbering on samd21E
2019-07-26 Huge update
    * Changes pin layout in arduino files which are now reflected in SAMD21 symbol
    * reroutes different lines to the headers on the left side of the board
    * removes the APA102 in favor of blue stat LED
    * Changes Qwiic Micro Arduino pin order and internal APA102 pin assignments
    * Adds gerbers
2019-08-12 New bootloader, updates samd21 with latest package
2019-08-12 Fixes SPI (wrong pins given to SPI defines)
2019-08-13 Moves the EEPROM chip and Lipo connector away from each other every so slightly.
2019-08-14 Moves 10k pull-up resistor on Flash CS line to top layer.
2019-08-14 Updates dimensions...
2019-08-15 Adds Circuit Python build files.
2019-08-16 Adds VCC ranges, Adds note for optional parts
2019-08-16 Moves wondering text
2019-08-16 Adds updated Production Files
2019-08-19 Updates Ignore pins in Circuit Python build
    * Changes USB PID to 0x8D24
    * Adds SUPEROPT flag
    * Adds UART pins to mpconfigboard.h
2019-08-19 Changes linker file selection for circuit python build, and adds flash spi for CP build as well
2019-08-19 Removes the flash pins in pins.c (outdated information)
2019-08-19 Adds a uf2 and elf file for a circuit python build using flash on the underside.
2019-08-19 Updates file structure, creates circuit python build if user does not have their own flash
2019-08-19 Adds circuit python firmware for those that do not use a flash.
2019-10-09 Adds new production files with correct design rules
2019-10-23 Adds corrected Graphical Datasheet
2019-10-23 Update Graphical Datasheet
    - Renamed file for product page
    - Export PNG image for hookup guide
    - Add Storefront SKU
2019-10-25 Move Graphical Datasheet
    Moving to GitHub Repo => https://github.com/sparkfun/Graphical_Datasheets/tree/master/Datasheets/SAM21
2020-07-28 Update variant.cpp
    Fixed the misordered pins 16 and 17
2021-04-05 Swaps "D16/D17" symbol names
